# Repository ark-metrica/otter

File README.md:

# otter
otter project delivery files

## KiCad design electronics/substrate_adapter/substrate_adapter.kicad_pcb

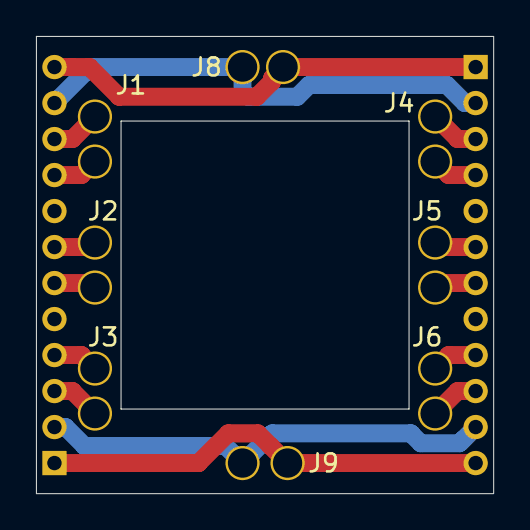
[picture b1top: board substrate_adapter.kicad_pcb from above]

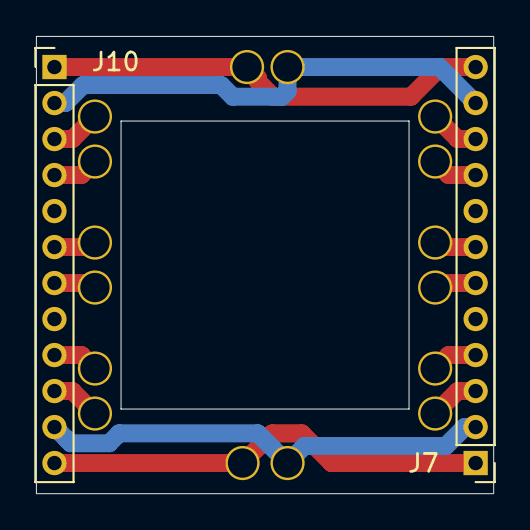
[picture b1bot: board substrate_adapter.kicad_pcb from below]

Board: 2 copper layers, 25.4 x 25.4 mm, 18 parts (2 on the bottom side), 16 nets.

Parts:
J1, J11: PIX1; spring_pin
J2, J12: PIX2; spring_pin
J3, J13: PIX3; spring_pin
J4, J16: PIX4; spring_pin
J5, J17: PIX5; spring_pin
J6, J18: PIX6; spring_pin
J7: L_CONN; PinHeader_1x12_P2.00mm_Vertical
J8, J15: TOP_TCE; spring_pin
J9, J14: BOT_TCE; spring_pin
J10: R_CONN; PinHeader_1x12_P2.00mm_Vertical

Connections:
unnamed: J1.1, J7.10
unnamed: J2.1, J7.7
unnamed: J3.1, J7.4
unnamed: J7.12, J10.1, J15.1
unnamed: J7.11, J8.1, J10.2
unnamed: J4.1, J10.3
unnamed: J10.4, J16.1
unnamed: J5.1, J10.6
unnamed: J10.7, J17.1
unnamed: J6.1, J10.9
unnamed: J10.10, J18.1
unnamed: J7.2, J10.11, J14.1
unnamed: J7.1, J9.1, J10.12
unnamed: J7.9, J11.1
unnamed: J7.6, J12.1
unnamed: J7.3, J13.1

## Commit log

2019-11-06 add high level connections
2019-11-06 reorg
2019-11-06 add some refrence docs
2019-11-07 substrate adapter
2019-11-07 update silk
2019-12-07 add some ray tracing drawings
2019-12-29 added dimensioned drawing of substrate holder
2019-12-30 update holder drawing
2019-12-31 fix dim drawing
2019-12-31 update holder dims
2020-01-07 add alignment drawing
2020-01-25 add adapter board pcb order zip
2020-01-25 add bom
2020-01-27 wip on bom
2020-02-08 added last holder assembly
2020-02-08 rename substrate holder step
2020-02-11 updated substrate holder
2020-02-12 removed old file
2020-02-13 latest substrate holder update
2020-02-17 updated holder with latest retainer
2020-06-12 move vagrant stuff over here
2020-11-25 firmware
2021-04-10 add 50x50 sketch
